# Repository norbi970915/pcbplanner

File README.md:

# pcbplanner

Browser-based calculators for PCB design with a compact shadcn/ui workbench: menu bar, document tabs, a Tools panel, a Properties panel for the inputs, and a status bar. Built with Vite, React, TypeScript, Tailwind CSS and shadcn/ui. The original category colors and PCB material colors are preserved.

## Tools

| Group | Tools |
|---|---|
| Signal integrity | Impedance (2D field solver: microstrip / coated / embedded / stripline / coplanar, SE and differential (edge-coupled and balanced shielded broadside), solve W or S, laminate library), Delay & timing, Termination, Trace loss (incremental-inductance conductor loss with Hammerstad / Groiss / Huray roughness, field-energy dielectric loss, Djordjevic–Sarkar Dk/Df), Crosstalk, Differential via, Via stitching & fence spacing, Interface rules, Phase noise & jitter, S-parameter viewer |
| RF | VSWR & return loss, Coax impedance, L-network matching, Quarter-wave & stubs |
| Stackup | Stackup advisor, Layer stack manager (178 rigid fabricator stackups, 2–12 layers, plus flex and rigid-flex starters), Materials (datasheet Dk/Df, solder masks, copper foil roughness) |
| Thermal | Junction temperature, Thermal vias, Copper heat spreading |
| Power & conductors | Trace width / current (IPC-2221, IPC-2152), Via, Skin effect, Fusing current, Wire gauge / drop, Conductor spacing (IPC-2221), Creepage & clearance (IEC 60664-1) |
| Power integrity | PDN, EMI filter |
| Power supply | Power tree, Buck converter (TI SLVA477B), Boost converter (TI SLVA372D), LDO dissipation, Feedback divider |
| Components | Spiral inductor, Padstack, SMD land pattern, BGA land, Resistor color code, SMD resistor code, Capacitor code |
| Electronics | Ohm's law, Reactance & resonance, RC filters, Active filters, Op-amp gain, Crystal & ppm, 555 timer, I²C pull-up, Logic levels, Comparator hysteresis, ADC input, NTC thermistor, Current-sense shunt, Resistor tools, Attenuator pads |
| Utilities | Unit converter, Reference charts |

The site also has 34 guides (`src/guides/`), a page per laminate datasheet (`src/data/materialPages.ts`) and a layout-guideline page per interface (`src/data/interfacePages.ts`).

Every tool keeps its inputs in the URL, so any result can be shared as a link.

## Interface

Shared components live in src/components/shadcn/. Workbench layout and page styles are in src/styles/workbench.css; dark/light theme and material colors are in src/index.css. The desktop app keeps docked tools and properties, and phones have an accessible tools drawer. The existing calculator, URL state and offline behavior are retained.

Favorite tools with the star in the sidebar or calculator heading. Favorites appear at the top of the tools panel, persist in localStorage on the same browser/device, and update across open tabs.

Run node scripts/audit-ui.mjs after starting the production preview to check all routes at desktop and phone sizes, theme switching, search, calculator reset and mobile navigation. Screenshots and the report are saved under dist-check/redesign/.

Run node scripts/audit-featured-carousel.mjs for the featured-tools carousel: all ten illustrations, three visible cards, arrows that move one tool at a time, free dragging and touch swiping with momentum, position indicator, keyboard navigation and dark/light mobile layouts. Its screenshots and report are saved under dist-check/carousel/.

Run node scripts/audit-favorites.mjs for favorites: sidebar and calculator toggles, browser-restart persistence, cross-tab updates, mobile navigation and unavailable storage. Its screenshots and report are saved under dist-check/favorites/.

Run node scripts/audit-broadside.mjs for broadside controls, width and spacing solving, URL sharing, vertical field polarity, mirrored plies, fabrication corners, mm/mil units, desktop/phone layouts and both themes. Its screenshots and report are saved under dist-check/broadside/.

Run `node scripts/audit-seo.mjs [baseURL]` to compare all static pages with their metadata catalogue and verify client navigation, history, clean canonical URLs, 404 indexing, delayed responses and offline metadata. Reports are saved under `dist-check/seo/`. Prerendering rejects unresolved description expressions and missing method exports. The generated metadata catalogue is versioned under `dist/assets/`, shared with the browser after navigation and cached by the existing service worker.

## Field solver

`src/lib/fieldsolver.ts` solves ∇·(ε∇φ) = 0 on a graded finite-volume mesh with Jacobi-preconditioned conjugate gradients. Edge-coupled pairs use the symmetry plane: a Neumann boundary gives single-ended / even mode and a Dirichlet boundary gives odd mode. Capacitance comes from field energy, and Z0 = 1/(c·√(C·C_air)). Broadside pairs use two vertically aligned, mirror-etched traces: opposite drive voltages for odd mode, equal voltages for even mode. The x symmetry boundary remains Neumann. The initial broadside model requires two ground planes and mirrored dielectrics; it excludes offsets and unbalanced or unshielded pairs. `src/lib/broadside.test.ts` checks parallel-plate limits, odd-mode half-height equivalence, dielectric scaling, convergence, target solving and balanced fabrication corners.

The solver runs in Web Workers; batch jobs such as the advisor use a worker pool.

It has been checked against:
- Hammerstad–Jensen and Wheeler formulas (within 2 %)
- a commercial 2D field solver for coated microstrip (within 1 % in six test cases)

## Stackup data

- `src/data/fabStackups.ts` holds 178 standard FR-4 stackups (2–12 layers, 0.8–2.0 mm), named by their outer prepreg glass style.
- Default layer roles (signal / plane) are assigned by layer count in `src/lib/stackups.ts` (`ROLE_PATTERNS`).

The layer stack manager also includes six editable flex and rigid-flex starters in `src/data/flexStackups.ts`. Regional membership references shared layer records, so copper and dielectric edits stay linked. The advisor evaluates each physical region separately, using its own thickness, reference planes and coverlay/adhesive plies. These are uniform cross-section models with solid planes; bends, transitions and hatched planes need separate validation. Material notes distinguish per-ply Dk/Df reference frequencies and the low-frequency Kapton film estimate.

PCBPlanner JSON exports and imports the complete linked construction. Existing CAD templates export one selected rigid region; coverlay/adhesive CAD export is explicitly unavailable.

Run `node scripts/audit-rigid-flex.mjs [baseURL]` against the production preview or live site for saving/importing, shared edits, region handoff, advisor solves and desktop/mobile themes. Screenshots and the report are written to `dist-check/rigid-flex/`.

## Development

```bash
npm install
npm run dev        # dev server
npm test           # vitest: formula, solver and advisor validation
npm run build      # production build in dist/
npm run preview    # serve dist/ on http://localhost:4173
node scripts/shots.mjs <outDir>   # browser smoke test + screenshots (needs Edge and a running preview)
```

## Deployment

Vercel builds `main` on every push (`vercel.json`). The build writes a static HTML page per route, so no SPA fallback is needed:

1. `scripts/gen-sitemap.mjs`: `public/sitemap.xml` and `robots.txt`. `lastmod` comes from each page's git history; without history the committed dates are kept, so commit the sitemap.
2. `tsc -b` and `vite build`.
3. `scripts/prerender.mjs`: one HTML file per tool, guide, material and interface page with its title, description, canonical URL, share image and JSON-LD; `404.html` (served with status 404); the guides Atom feed `/guides/feed.xml`.
4. `scripts/gen-sw.mjs`: `sw.js`, the service worker for offline use and installation.

Share images in `public/og/` are rendered by `node scripts/render-og.mjs` (needs Edge); run it after changing a title or summary. Search engines are notified through IndexNow after each production deploy (`.github/workflows/indexnow.yml`, `scripts/indexnow.mjs`).

## Monetisation hooks

- No advertising or affiliate links for now. Add them in `src/components/ToolPage.tsx` when needed.
- The app name is set in `src/config.ts`.

Run `node scripts/audit-diagrams.mjs [baseURL]` to verify the impedance/trace-loss cross-sections, RC circuit, thermal pad and padstack illustrations in both themes at desktop, 390 px and 320 px. Checks cover SVG label bounds, unique paint IDs, live input annotations, thermal pad proportions, mm/mil units and geometry variants. Screenshots and the report are saved under `dist-check/diagrams/`.

Run `node scripts/audit-workbench.mjs [baseURL]` for the compact Home card, persistent Properties-panel resizing, buck/boost switch-phase illustrations, crosstalk spacing annotations and mobile input/result navigation. It checks both themes at 1600, 1024, 390 and 320 px. Screenshots and the report are saved under `dist-check/workbench/`.

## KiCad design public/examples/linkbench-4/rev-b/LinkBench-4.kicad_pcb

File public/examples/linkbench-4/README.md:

# LinkBench-4 — PCB Planner demonstration

Original passive four-lane differential interconnect with a separate 5 V resistive load bank.
Open `LinkBench-4.kicad_pro` in KiCad 10, or load the board and project files together in
https://www.pcbplanner.com/kicad-project. The schematic is included.

## Board and operating assumptions

- Chamfered 70 × 50 mm board with four copper layers, two inner ground planes and four differential pairs.
- Three pairs run on F.Cu; LANE2 transitions to B.Cu with nearby return vias.
- The net class assigns a 100 Ω differential target. The passive headers and board do not establish
  compliance with any protocol or data rate.
- Outer copper: 35 µm; inner copper: 18 µm. Dielectrics: 0.110 / 0.674 / 0.110 mm,
  Dk 4.2 and loss tangent 0.018. Total thickness including masks: 1.03 mm.
- Coupled trace width / edge gap: 0.135 / 0.165 mm. This is an illustrative stackup,
  rather than a fabrication house's qualified construction.
- J3 supplies +5 V (pin 1) and GND (pin 2). R1–R4 are four parallel 68 Ω loads,
  nominally 73.529 mA and 0.367647 W each at 5 V: 294.118 mA / 1.470588 W total.
  The intended physical resistors are rated at least 1 W each.
- The Power example uses constant load currents at nominal supply, GND return and 25 °C ambient.
- The Thermal example uses those four heat sources, copper losses, a flat board in still air,
  emissivity 0.9 and laminate conductivities 0.8 / 0.35 W/m·K (in-plane / through-plane).
  Press Solve in Thermal. Maps are steady-state board estimates, not measurements,
  resistor surface temperatures or junction temperatures.

J2's physical orientation reverses the signal pin order: check the schematic before connecting
external equipment. The board has no transmitter or receiver. Validate materials, connector
effects, manufacturing tolerances and complete link performance before making hardware.

## Revision comparison

The root project is revision A. `rev-b/` contains revision B, with the same schematic and netlist:

1. LANE0's centre dogleg moves 0.6 mm on both traces.
2. The two 5 V input-feed segments widen from 0.4 to 0.8 mm.
3. Two GND stitching vias are added at (123, 85.8) and (128, 85.8) mm.
4. The top +5 V pour extends 0.8 mm toward the signal region.
5. The silkscreen revision changes from A to B.

`gerbers/rev-a/` and `gerbers/rev-b/` are native KiCad exports of top and bottom copper,
both inner copper layers, top silkscreen and Edge.Cuts. These are inspection sets; they
do not contain all manufacturing outputs, solder masks, paste or drill files.
Select matching layers when comparing. The outline is unchanged. Added vias and their
clearances affect other copper layers too. Gerber changes describe geometry, not an
electrical sign-off.

Both boards were checked with KiCad 10.0.4: zero DRC violations, zero unconnected items
and zero schematic-parity issues. Zones were filled by KiCad. No DRC exclusions were added.
These checks cover the configured rules and do not qualify the board for production.

## Source and regeneration

The layout and schematic were created for PCB Planner. Standard KiCad library symbols,
footprints and models are used. No third-party demo board design is included.
`scripts/generate-linkbench-gerbers.py` in the PCB Planner source repository creates revision B
from revision A, refills its zones, runs DRC/parity and exports both Gerber sets using KiCad 10.

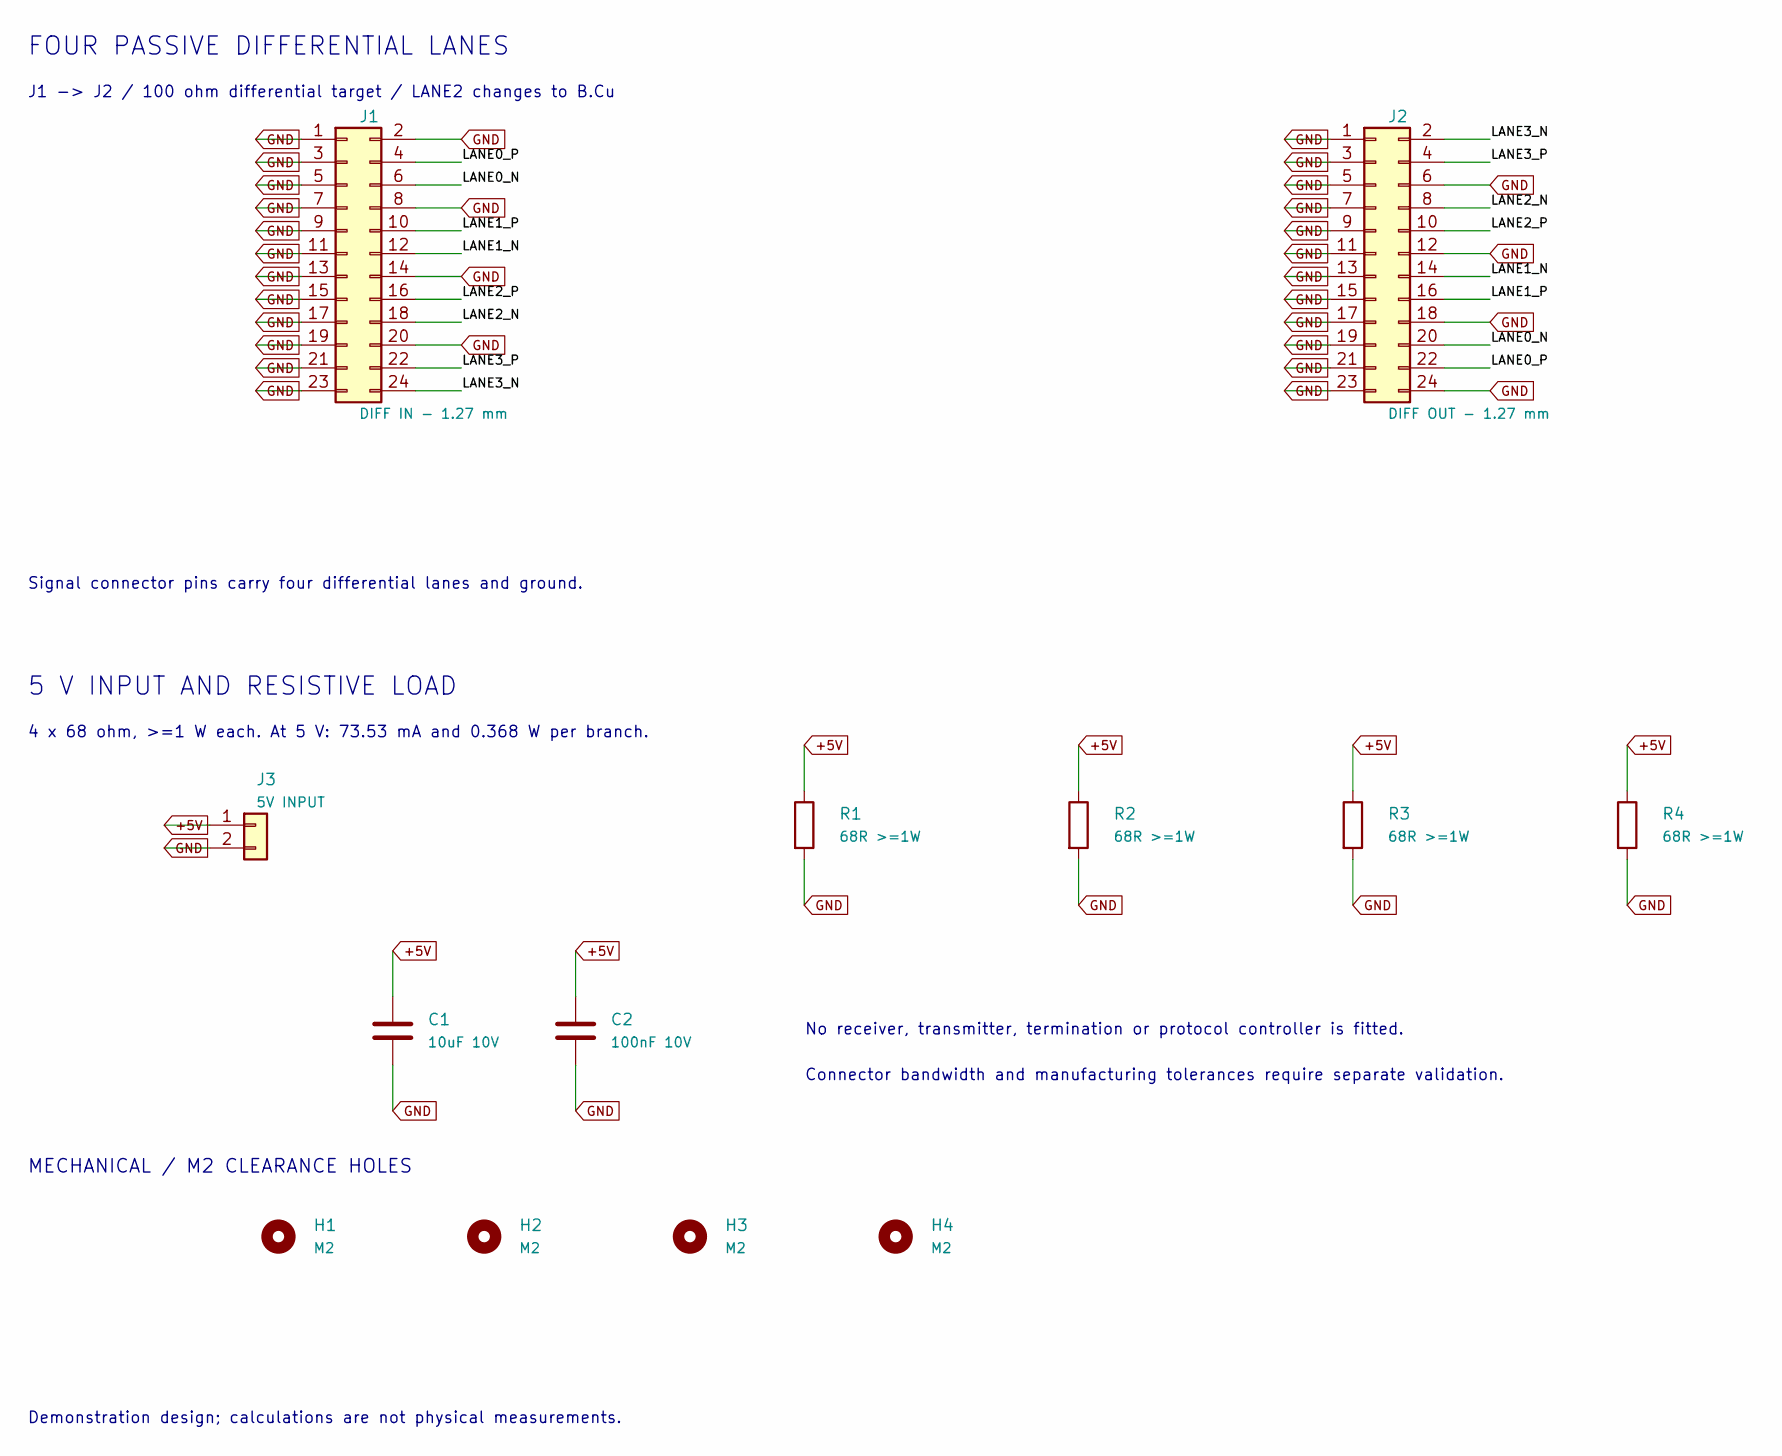
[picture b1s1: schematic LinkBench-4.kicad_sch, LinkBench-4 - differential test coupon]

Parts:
C1: 10uF 10V; C_0805_2012Metric
C2: 100nF 10V; C_0603_1608Metric
H1, H2, H3, H4: M2; MountingHole_2.2mm_M2
J1: DIFF IN - 1.27 mm; PinHeader_2x12_P1.27mm_Vertical_SMD
J2: DIFF OUT - 1.27 mm; PinHeader_2x12_P1.27mm_Vertical_SMD
J3: 5V INPUT; PinHeader_1x02_P2.54mm_Vertical
R1, R2, R3, R4: 68R >=1W; R_2512_6332Metric

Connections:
+5V: C1.1, C2.1, J3.1, R1.1, R2.1, R3.1, R4.1
/LANE0_N: J1.6, J2.20
/LANE0_P: J1.4, J2.22
/LANE1_N: J1.12, J2.14
/LANE1_P: J1.10, J2.16
/LANE2_N: J1.18, J2.8
/LANE2_P: J1.16, J2.10
/LANE3_N: J1.24, J2.2
/LANE3_P: J1.22, J2.4
GND: C1.2, C2.2, J1.1, J1.2, J1.3, J1.5, J1.7, J1.8, J1.9, J1.11, J1.13, J1.14, J1.15, J1.17, J1.19, J1.20, J1.21, J1.23, J2.1, J2.3, J2.5, J2.6, J2.7, J2.9, J2.11, J2.12, J2.13, J2.15, J2.17, J2.18, J2.19, J2.21, J2.23, J2.24, J3.2, R1.2, R2.2, R3.2, R4.2

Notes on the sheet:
FOUR PASSIVE DIFFERENTIAL LANES
J1 -> J2 / 100 ohm differential target / LANE2 changes to B.Cu
Signal connector pins carry four differential lanes and ground.
5 V INPUT AND RESISTIVE LOAD
4 x 68 ohm, >=1 W each. At 5 V: 73.53 mA and 0.368 W per branch.
No receiver, transmitter, termination or protocol controller is fitted.
Connector bandwidth and manufacturing tolerances require separate validation.
MECHANICAL / M2 CLEARANCE HOLES
Demonstration design; calculations are not physical measurements.

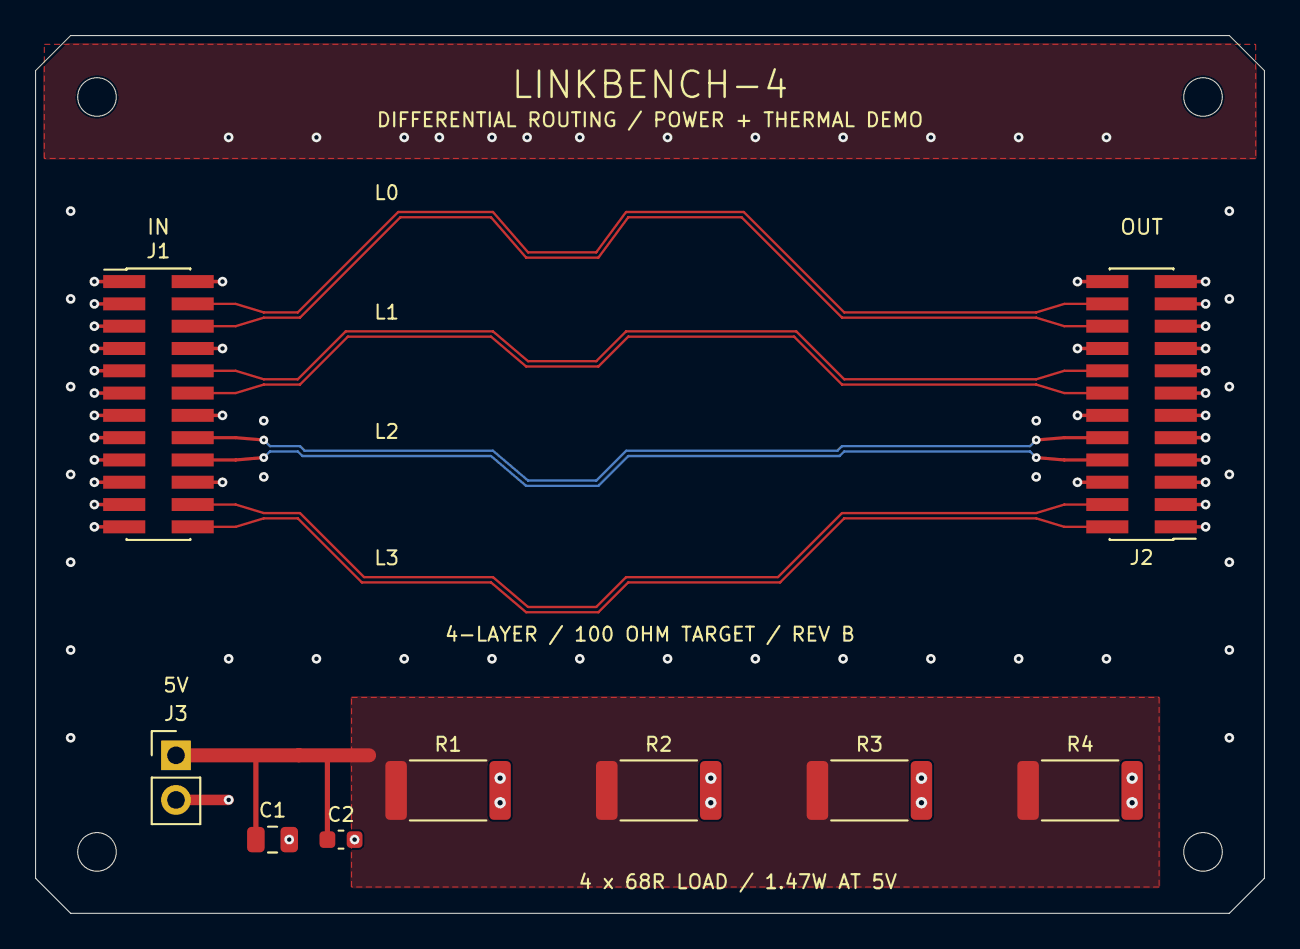
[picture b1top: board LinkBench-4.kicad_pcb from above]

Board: 4 copper layers, 70.0 x 50.0 mm, 13 parts (0 on the bottom side), 10 nets.

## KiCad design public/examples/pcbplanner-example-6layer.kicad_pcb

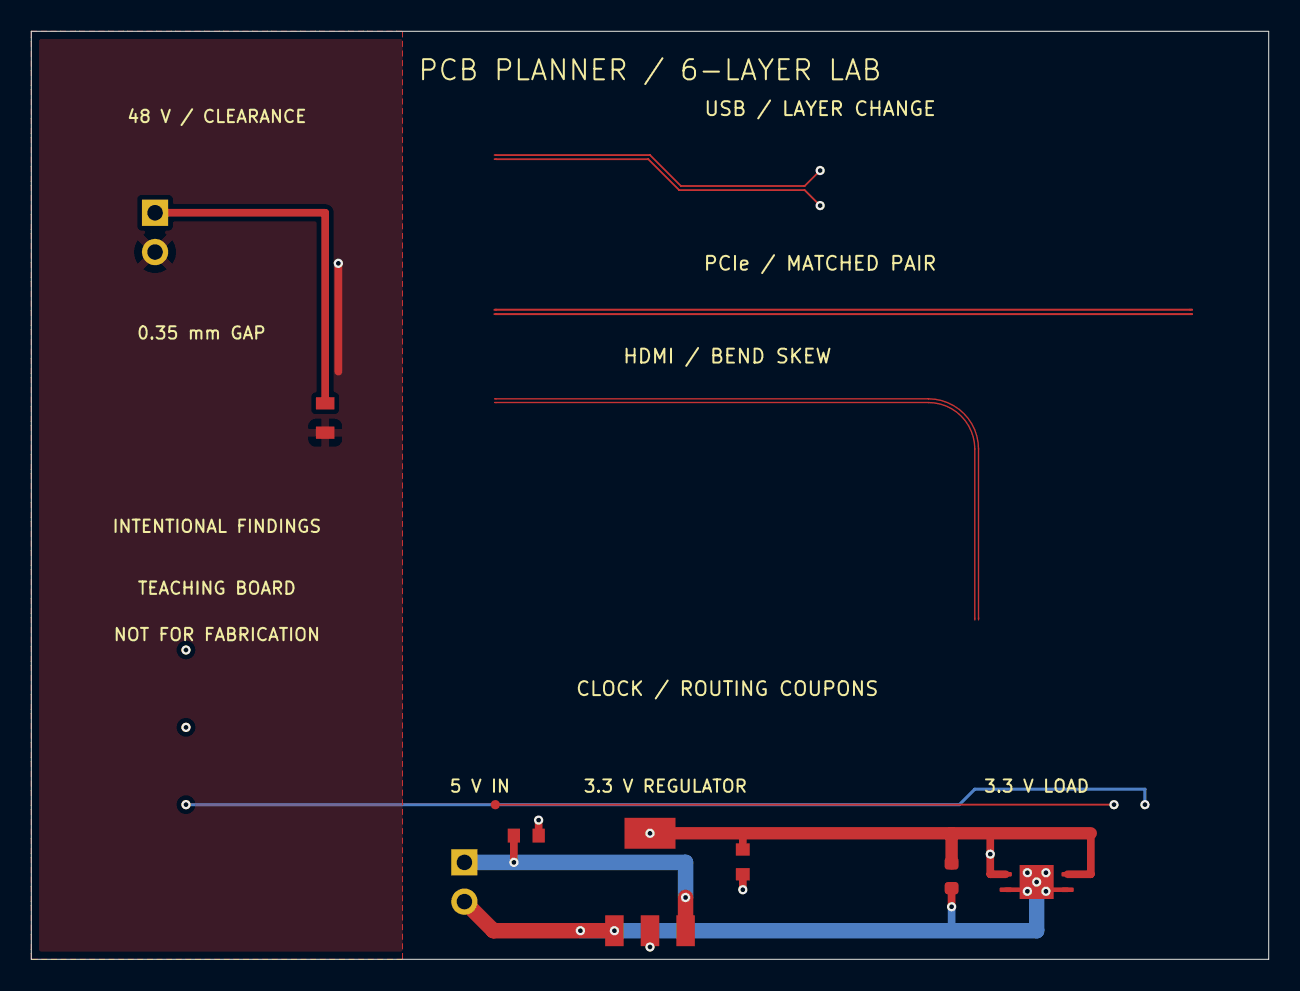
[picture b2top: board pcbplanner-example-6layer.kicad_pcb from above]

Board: 6 copper layers, 80.0 x 60.0 mm, 17 parts (0 on the bottom side), 10 nets.

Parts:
C1: 10uF; C_0603_1608Metric
C2: Input bulk (demo); C_0603_1608Metric
C3: Output bulk (demo); C_0603_1608Metric
J1: +5V in; PinHeader_1x02_P2.54mm_Vertical
J2, J3, J4, J5, J6: Routing coupon; Routing_Coupon_Pads
J8: 48V clearance coupon; PinHeader_1x02_P2.54mm_Vertical
R1: 10k (clearance coupon); R_0805_2012Metric
TP1, TP4: CLK; TestPad
TP2, TP3: SDA; TestPad
U1: 3.3V regulator (demo); SOT-223-3_TabPin2
U2: 3.3V load (demo); Demo_Load_ExposedPad

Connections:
+3V3: C1.1, C3.1, U1.2, U2.1, U2.3
+5V: C2.1, J1.1, U1.3
+48V: J8.1, R1.1
/CLK: TP1.1, TP4.1
/HDMI_D0+: J5.1, J6.1
/HDMI_D0-: J5.2, J6.2
/PCIE_TX0_N: J2.2, J3.2
/PCIE_TX0_P: J2.1, J3.1
/SDA: TP2.1, TP3.1
GND: C1.2, C2.2, C3.2, J1.2, J8.2, R1.2, U1.1, U2.2, U2.4, U2.5
